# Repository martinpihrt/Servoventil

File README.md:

# Servoventil
Servoventil pro zalévací systém řízený procesorem ATTINY 1634 napájený z 5 AA baterií (celkem 6V). Zařízení je postavené z SMD součástek jako finální produkt za co nejméně peněz. Schéma zapojení obsahuje pouze nejnutněší součástky a procesor, který není zbytečně velký (rozměrově a programově). Deska obsahuje DIP spínač pro nastavení časů.  Programovací konektor ICSP 2x5 pinů, LED signalizující vybité baterie a chod zařízení, konektor pro připojení serva MG996R, startovací tlačítko, konektor pro sériovou linku (možnost komunikace s procesorem). Program pro procesor je napsán v prostředí Arduino IDE.  
Cena celého zařízení vychází bez serva na cca 225 Kč.

* Pohled na osazenou desku HW:1.0
<br>
* Schéma zapojení HW:1.0
<br>

# Funkce
## Uvedení do provozu
Po připojení napájení (5ks nabíjecí baterie AA 1,2V - celkem tedy 6-7V) čeká zařízení na stisk tlačítka. V tomto režimu neodebírá žádný proud z baterií (oba MOSFET tranzistory jsou udržovány uzavřené přes rezistory z kladného pólu). Časovač RTC ještě nebyl nastaven a má vloženu záložní baterii. Po stisknutí tlačítka na minimálně 1 sec se uzemní řídící vstup (gate) MOSFET tranzistoru, ten se otevře a přivede napájecí napětí na stabilizátor 3,3V. Za stabilizátorem je připojen procesor ATTINY 1634, který provede toto:
* sepne pomocný tranzistor, který podrží sepnutý (gate) u MOSFETu i po uvolnění tlačítka.
* změří napětí baterie (na AD vstupu procesoru je napětí z baterií 0-6V sníženo rezistorovým děličem na rozsah 0-3,3V). Napětí baterie se pohybuje (naprázdno) plně nabitého článku 1,4 V až napětí vybitého článku 1,0 V. Napětí pod 5V lze považovat za vybitý stav. Na AD vstupu naměříme hodnotu napětí (po zmenšení děličem) 2,6V. Pokud je baterie vybitá bliká LED dioda (3x blik, pauza, 3x blik...). RTC běží pouze z baterie a když je čas alarmu tak RTC přes svůj vnitřní tranzistor (otevřený kolektor) uzemní MOSFET, který sepne napájení pro stabilizátor a CPU. 
* přečte nastavené DIP spínače, sepne na určitý čas servo (napájení serva přes MOSFET a generuje signál pro odpovýdající směr a rychlost serva na určitou dobu) LED svítí -> ventil se otevře. Následně vypne napájení serva a čeká nastavenou dobu (dle DIP spínače 1-7 minut). Led bliká po dobu čekání otevření ventilu (krátké záblesky). Po nastavené době opět sepne napájení serva a ventil uzavře (LED svítí).
* nastaví čas (alarm) do RTC pro příští probuzení zařízení (cyklus 12, nebo 24 hodin).
* vypne veškeré napájení (běží pouze RTC z baterie).
* po nastavené době (DIP pozice 4: 12/24 hodin) RTC probudí CPU a opět se provede otevření ventilu na určitou dobu...

## DIP spínač má následující význam
Pozice 1-3 je BCD (dvojkový) kód pro nastvení doby otevření ventilu 1-7 minut.
* pozice 1 -> ON=1 minuta
* pozice 2 -> ON=2 minuty
* pozice 3 -> ON=4 minuty
Výsledný čas dle pozice 1-3 se sčítá. Příklad: čas otevření ventilu chceme 3 minuty -> DIP pozice 1 = ON, pozice 2 = ON, pozice 3 = OFF

Pozice 4 je čas probouzení.
* pozice 4 -> ON= 12 hodin, OFF= 24 hodin probouzení RTC časovače.

## Osazení desky spojů
Deska byla vyrobena u https://www.allpcb.com/.
* Pohled na desku TOP
<br>
* Pohled na desku BOT
<br>
První čím začneme je osazení SMD součástek z horní strany (TOP) a následně spodní (BOTTOM) strany. Po osazení SMD součástek zapájíme z horní strany THT (drátové) součástky - DIP spínače, držák baterie, napájecí konektor, řadové lišty. Před připojením napájení (baterie, nebo ICSP konektor) je potřeba desku pečlivě zkontrolovat na případné zkraty, nebo otočení součástek. Značení SMD rezistorů je následující: příklad text na rezistoru 1014 znamená 101 + 4 nuly tedy 101 0000 Ohmů, nebo 202 znamená 20 + 2 nuly tedy 20 00 Ohmů (2k).
Před připojením baterií (5ks AA) připojíme (pokud máme) napájecí zdroj s proudovou pojistkou, kterou nastavíme na 100 mA při 6V. Servo ani ICSP programátor není zatím k desce připojen. Obvod nemá v tuto chvíli ze zdroje odebírat žádný proud. Stiskneme a držíme tlačítko SW1 zmačknuté. Multimetrem (voltmetrem) změříme napětí na procesoru, RTC nebo stabilizátoru 3,3V. Napětí musí být cca 3,3V (při 6V na zdroji). Proud ze zdroje bude stále nepatrný (pár mA) - pouze se napájí procesor. Pokud se neobjevil problém (zkrat, velký podezřelý odběr proudu ze zdroje atd...) můžeme odpojit zdroj a zkusit připojit ICSP programátor. Nastavíme Arduino IDE na správný procesor a ICSP programátor. V tuto chvíli by již měl jít do procesoru nahrávat kód. Pokud připojíme na UART (sériovou linku) převodník, můžeme sledovat ladící výpisy co se aktuálně v procesoru odehrává. Protože je RTC obvod DS3231 jako samostatná součástka velmi drahý (okolo 200,-), tak ho odpájíme z China desky (ta se dá pořídit za 30,-).
* Pohled na osazenou desku TOP
<br>
* Pohled na osazenou desku BOT
<br>
* Připojení ICSP programátoru a USB-UART převodníku
<br>
<br>
* Deska RTC s DS3231 (před vypájením a po vypájení)
<br>
<br>

## Přidání podpory pro procesor ATTINY 1634 do Arduino IDE
Spustíme nainstalované Arduino v našem počítači a otevřeme záložku "Soubor -> vlastnosti" a do správce dalších desek URL přidáme tento odkaz
http://drazzy.com/package_drazzy.com_index.json ze stránek [GitHub drazzy](https://github.com/SpenceKonde/ATTinyCore/blob/master/Installation.md). Následně potvrdíme tlačítkem "OK". Otevřeme v Arduinu záložku "Nástroje -> Vývojová deska -> Manažér desek" v otevřeném seznamu si vybereme "ATTinyCore by Spencle Konde" a přidáme do Arduina tlačítkem "instalace". V nastavení Arduino IDE je po těchto krocích možné využívat i jiné procesory než které jsou ve výchozí instalaci Arduina.

## Nahrání programu do desky - ICSP programátor
Připojíme do konektoru ICSP desky servoventilu náš programátor (pokud ho nemáme zakoupený, můžeme si ho vyrobit dle [tohoto návodu](https://pihrt.com/elektronika/390-programator-atmel-isp-usbasp)). Při připojení programátoru nepoužíváme napájení z baterií (baterie odpojíme)!

# Verze FW
* 1.0.0 výchozí verze programu 
* 0.0.0 výchozí verze programu - test všech periferií

# Verze HW
* 1.0 15.1.2019 výchozí verze desky 

# Licence
Creative Commons Attribution Share Alike 4.0
cc-by-sa-4.0

Na projektu se podílejí:
HW a FW Martin Pihrt - www.pihrt.com

# Aktuálně, TODO
## 23.4.2020
* Pracuji na verzi FW 1.0.0 (funkce dle popisu DIP a uvedení do provozu)

## 18.2.2019
* HW je otestován a plně funkční: pro test použit FW:0.0.0. Článek NiMh má 1,2 V. Napětí (naprázdno) plně nabitého článku je 1,4 V. Napětí vybitého článku je 1,0 V. Máme 5 článků -> napětí se bude pohybovat od 5V do 7V. Pod 5V je vybito LED blikne 2x krátce. Běží program - LED bliká rychle.

Výpis ze seriové linky (2 minuty probouzení)  
FW:0.0.0,18.2.2019,11:13:33  
RTC init...OK  
DIP1-4 init...OK  
DIP1=0 DIP2=1 DIP3=0 DIP4=1  
Baterie=5.86V  
Servo init...OK  
RTC nastavuji interval...OK  
Baterie=5.78V  
Baterie=5.85V  
Vypinam!

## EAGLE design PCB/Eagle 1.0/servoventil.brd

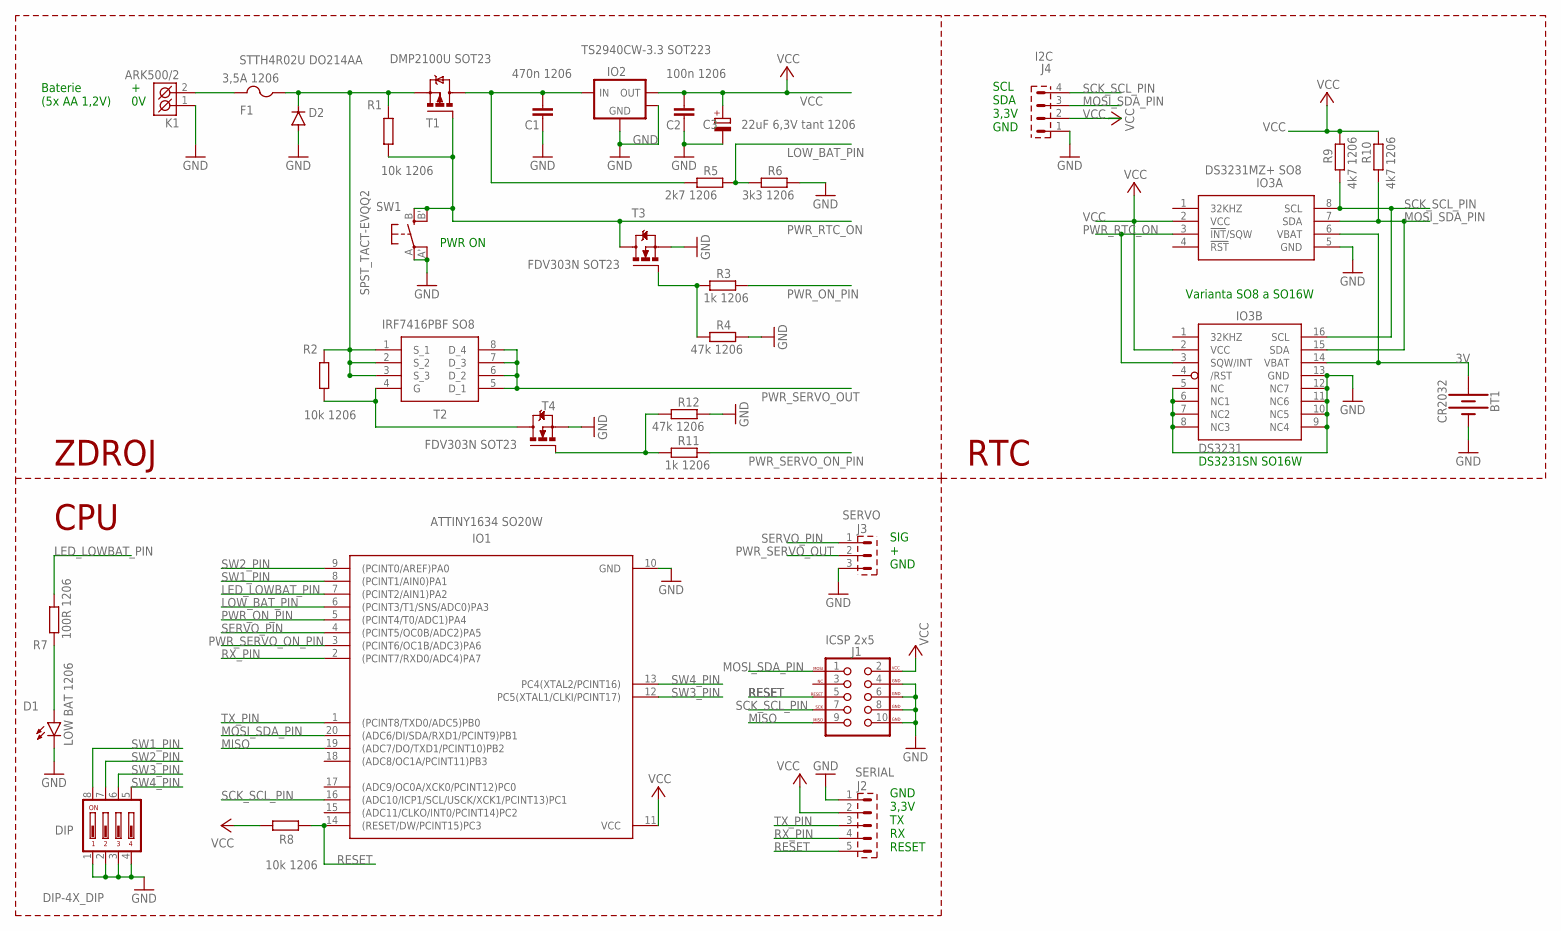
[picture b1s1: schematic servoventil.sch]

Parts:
BT1: CR2032; BATTCOM_20MM_PTH
C1: 470n 1206; C1206
C2: 100n 1206; C1206
C3: 22uF 6,3V tant 1206; CT3216
D1: LOW BAT 1206; LED-1206
D2: STTH4R02U DO214AA; DO214AA
DIP: DIP-4X_DIP; DIP-4X
F1: 3,5A 1206; R1206
IO1: ATTINY1634 SO20W; SOIC20
IO2: TS2940CW-3.3 SOT223; SOT-223-3
IO3A: DS3231MZ+ SO8; SOIC127P600X175-8N
IO3B: DS3231SN SO16W; SO16W
J1: ICSP 2x5; 2X5-SHROUDED_LOCK
J2: SERIAL; S1G5_JUM
J3: SERVO; S1G3_JUM
J4: I2C; S1G4_JUM
K1: ARK500/2
R1, R2, R8: 10k 1206; R1206
R3, R11: 1k 1206; R1206
R4, R12: 47k 1206; R1206
R5: 2k7 1206; R1206
R6: 3k3 1206; R1206
R7: 100R 1206; R1206
R9, R10: 4k7 1206; R1206
SW1: SPST_TACT-EVQQ2; EVQ-Q2
T1: DMP2100U SOT23; SOT-23
T2: IRF7416PBF SO8; SOIC127P600X175-8N
T3, T4: FDV303N SOT23; SOT-23

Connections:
3V: BT1.1 (+), IO3A.6 (VBAT), IO3B.14 (VBAT)
6V: C1.1, IO2.1 (VIN), R5.2, T1.3 (D)
GND: BT1.2 (-), C1.2, C2.2, C3.-, D1.C, D2.A, DIP.1, DIP.2, DIP.3, DIP.4, IO1.10 (GND), IO2.2 (GND), IO2.4 (HEATSINK), IO3A.5 (GND), IO3B.5 (NC), IO3B.6 (NC1), IO3B.7 (NC2), IO3B.8 (NC3), IO3B.9 (NC4), IO3B.10 (NC5), IO3B.11 (NC6), IO3B.12 (NC7), IO3B.13 (GND), J1.4 (GND), J1.6 (GND), J1.8 (GND), J1.10 (GND), J2.1, J3.3, J4.1, K1.1 (K1), R4.1, R6.1, R12.1, SW1.A, SW1.A' (P1), T3.2 (S), T4.2 (S)
LED_LOWBAT_PIN: IO1.7 ((PCINT2/AIN1)PA2), R7.1
LOW_BAT_PIN: IO1.6 ((PCINT3/T1/SNS/ADC0)PA3), R5.1, R6.2
MISO: IO1.19 ((ADC7/DO/TXD1/PCINT10)PB2), J1.9 (MISO)
MOSI_SDA_PIN: IO1.20 ((ADC6/DI/SDA/RXD1/PCINT9)PB1), IO3A.7 (SDA), IO3B.15 (SDA), J1.1 (MOSI), J4.3, R10.2
unnamed: F1.2, K1.2 (K2)
unnamed: D2.C, F1.1, R1.2, R2.2, T1.2 (S), T2.1 (S_1), T2.2 (S_2), T2.3 (S_3)
unnamed: R3.2, R4.2, T3.1 (G)
unnamed: R2.1, T2.4 (G), T4.3 (D)
unnamed: R11.2, R12.2, T4.1 (G)
unnamed: D1.A, R7.2
PWR_ON_PIN: IO1.5 ((PCINT4/T0/ADC1)PA4), R3.1
PWR_RTC_ON: IO3A.3 (!INT!/SQW), IO3B.3 (SQW/INT), R1.1, SW1.B (S), SW1.B' (S1), T1.1 (G), T3.3 (D)
PWR_SERVO_ON_PIN: IO1.3 ((PCINT6/OC1B/ADC3)PA6), R11.1
PWR_SERVO_OUT: J3.2, T2.5 (D_1), T2.6 (D_2), T2.7 (D_3), T2.8 (D_4)
RESET: IO1.14 ((RESET/DW/PCINT15)PC3), J1.5 (RESET), J2.5, R8.2
RX_PIN: IO1.2 ((PCINT7/RXD0/ADC4)PA7), J2.4
SCK_SCL_PIN: IO1.16 ((ADC10/ICP1/SCL/USCK/XCK1/PCINT13)PC1), IO3A.8 (SCL), IO3B.16 (SCL), J1.7 (SCK), J4.4, R9.2
SERVO_PIN: IO1.4 ((PCINT5/OC0B/ADC2)PA5), J3.1
SW1_PIN: DIP.8, IO1.8 ((PCINT1/AIN0)PA1)
SW2_PIN: DIP.7, IO1.9 ((PCINT0/AREF)PA0)
SW3_PIN: DIP.6, IO1.12 (PC5(XTAL1/CLKI/PCINT17))
SW4_PIN: DIP.5, IO1.13 (PC4(XTAL2/PCINT16))
TX_PIN: IO1.1 ((PCINT8/TXD0/ADC5)PB0), J2.3
VCC: C2.1, C3.+, IO1.11 (VCC), IO2.3 (VOUT), IO3A.2 (VCC), IO3B.2 (VCC), J1.2 (VCC), J2.2, J4.2, R8.1, R9.1, R10.1

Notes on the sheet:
+ 0V
Baterie (5x AA 1,2V)
ZDROJ
CPU
RTC
GND 3,3V TX RX RESET
PWR ON
Varianta SO8 a SO16W
DS3231SN SO16W
SIG + GND
SCL SDA 3,3V GND

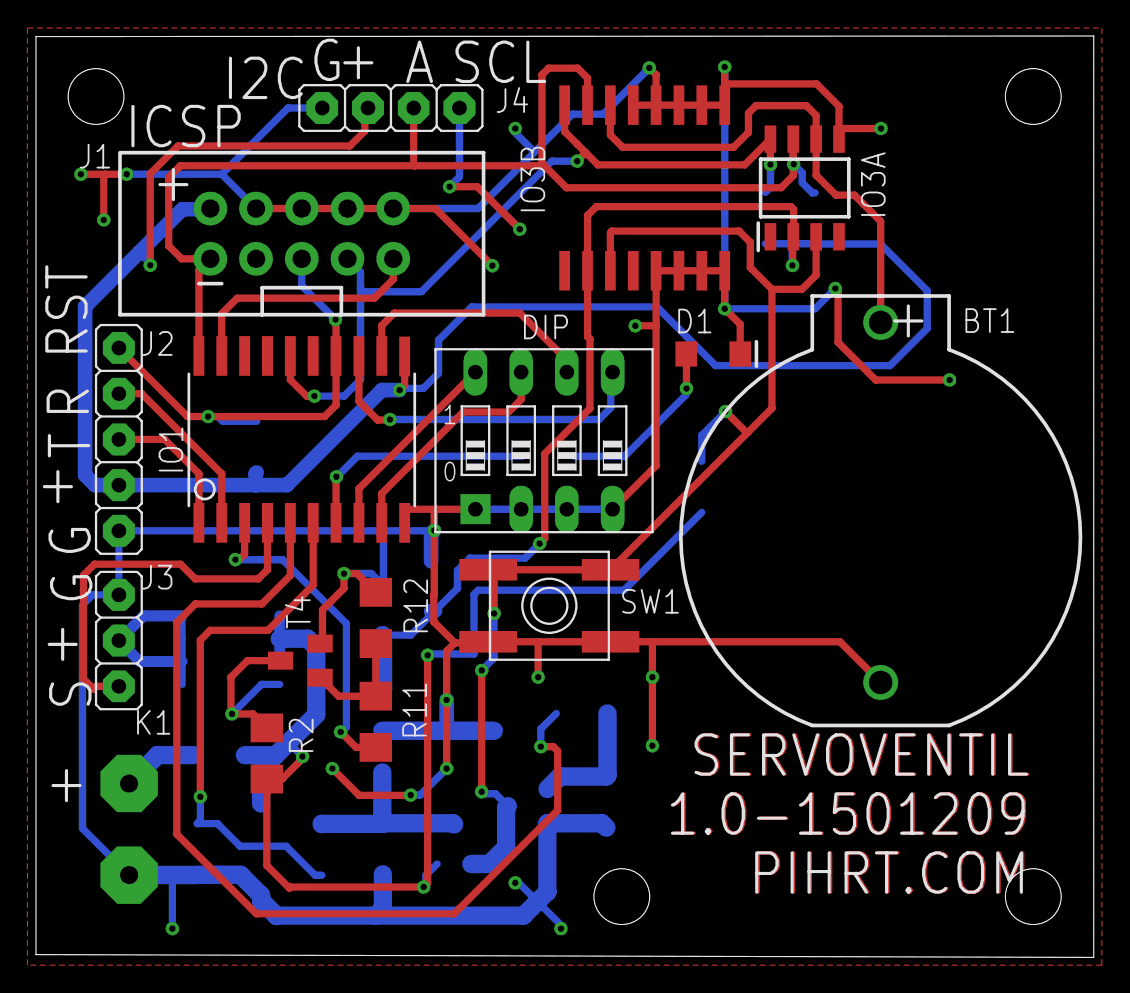
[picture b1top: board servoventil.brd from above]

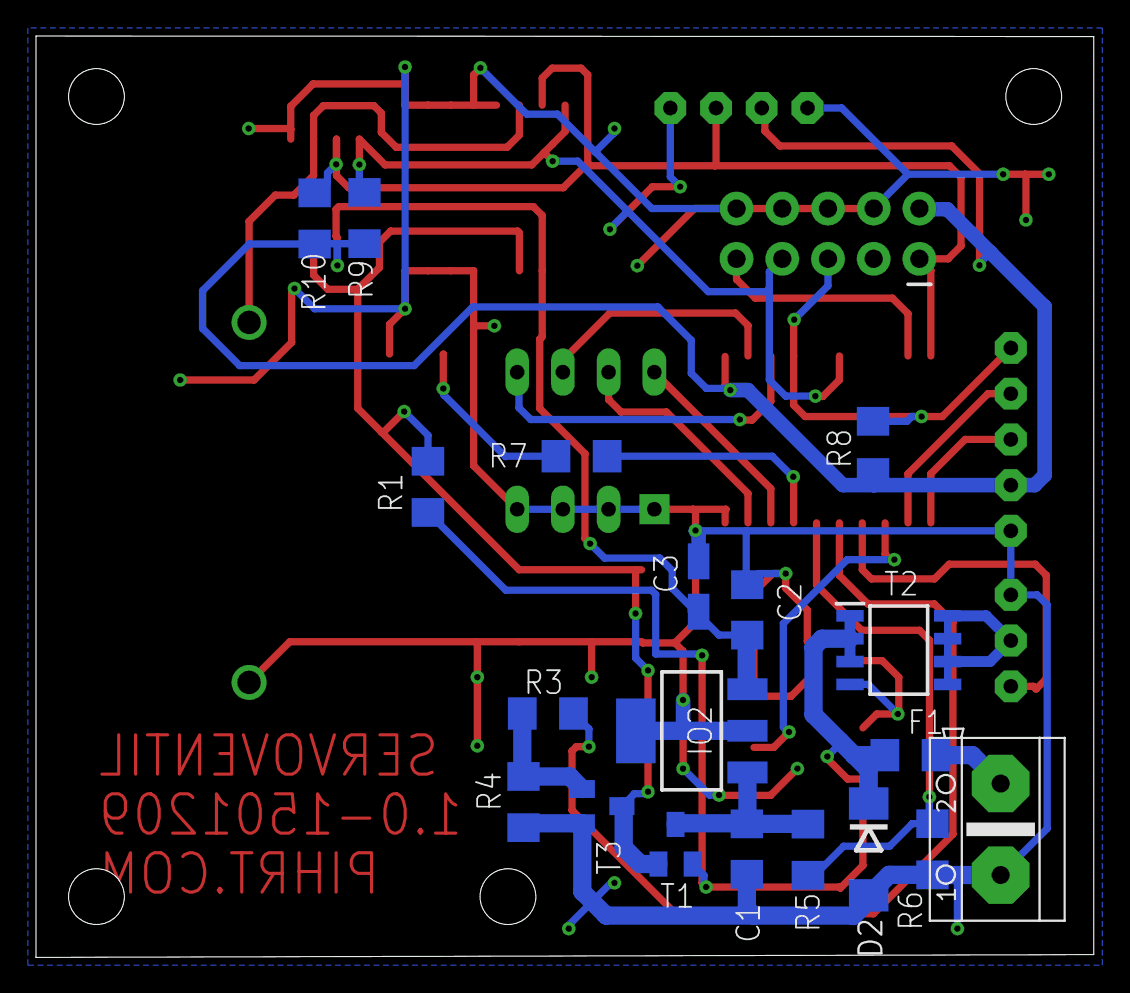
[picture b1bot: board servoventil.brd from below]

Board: 2 copper layers, 58.8 x 51.2 mm, 34 parts (19 on the bottom side), 27 nets.

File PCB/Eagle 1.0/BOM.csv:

"Part";"Value";"Device";"Package";"Description";"";
"BT1";"CR2032";"BATTERY-20MM_PTH";"BATTCOM_20MM_PTH";"Battery - Single Cell";"";
"C1";"470n 1206";"C-EUC1206";"C1206";"CAPACITOR, European symbol";"";
"C2";"100n 1206";"C-EUC1206";"C1206";"CAPACITOR, European symbol";"";
"C3";"22uF 6,3V tant 1206";"CPOL-EUCT3216";"CT3216";"POLARIZED CAPACITOR, European symbol";"";
"D1";"LOW BAT 1206";"LED1206";"LED-1206";"LED (Generic)";"";
"D2";"STTH4R02U  DO214AA";"DIODE-DO214AA";"DO214AA";"DIODE";"";
"DIP";"DIP-4X_DIP";"DIP-4X_DIP";"DIP-4X";"DIP Prepinac - 4x";"";
"F1";"3,5A 1206";"PTCFUSE-1206";"R1206";"PTC fuses, resettable thermistors";"";
"IO1";"ATTINY1634 SO20W";"ATTINY1634-SU";"SOIC20";"ATtiny1634";"";
"IO2";"TS2940CW-3.3 SOT223";"MCP1825_SOT223";"SOT-223-3";"Microchip MCP1824 LDO Voltage Regulator";"";
"IO3A";"DS3231MZ+ SO8";"DS3231MZ+";"SOIC127P600X175-8N";"Real Time Clock 5+/-ppm RTC";"";
"IO3B";"DS3231SN SO16W";"DS3231/SO";"SO16W";"";"";
"J1";"ICSP 2x5";"AVR_SPI_PROG_5X2LOCK";"2X5-SHROUDED_LOCK";"AVR 10-pin ICSP Header";"";
"J2";"SERIAL";"S1G5_JUMP";"S1G5_JUM";"Radove konektory - koliky - 5x";"";
"J3";"SERVO";"S1G3_JUMP";"S1G3_JUM";"Radove konektory - koliky - 3x";"";
"J4";"I2C";"S1G4_JUMP";"S1G4_JUM";"Radove konektory - koliky - 4x";"";
"K1";"ARK500/2";"ARK500/2";"ARK500/2";"Svorkovnice - roztec 5mm - dvojita";"";
"R1";"10k 1206";"R-EU_R1206";"R1206";"RESISTOR, European symbol";"";
"R2";"10k 1206";"R-EU_R1206";"R1206";"RESISTOR, European symbol";"";
"R3";"1k 1206";"R-EU_R1206";"R1206";"RESISTOR, European symbol";"";
"R4";"47k 1206";"R-EU_R1206";"R1206";"RESISTOR, European symbol";"";
"R5";"2k7 1206";"R-EU_R1206";"R1206";"RESISTOR, European symbol";"";
"R6";"3k3 1206";"R-EU_R1206";"R1206";"RESISTOR, European symbol";"";
"R7";"100R 1206";"R-EU_R1206";"R1206";"RESISTOR, European symbol";"";
"R8";"10k 1206";"R-EU_R1206";"R1206";"RESISTOR, European symbol";"";
"R9";"4k7 1206";"R-EU_R1206";"R1206";"RESISTOR, European symbol";"";
"R10";"4k7 1206";"R-EU_R1206";"R1206";"RESISTOR, European symbol";"";
"R11";"1k 1206";"R-EU_R1206";"R1206";"RESISTOR, European symbol";"";
"R12";"47k 1206";"R-EU_R1206";"R1206";"RESISTOR, European symbol";"";
"SW1";"SPST_TACT-EVQQ2";"SPST_TACT-EVQQ2";"EVQ-Q2";"SMT 6mm switch, EVQQ2 series";"";
"T1";"DMP2100U SOT23";"MOSFET-P-SOT23";"SOT-23";"P-Channel MOSFET with integrated body diode";"";
"T2";"IRF7416PBF SO8";"IRF7416PBF";"SOIC127P600X175-8N";"MOSFET P-Channel 30V 10A HEXFET SOIC8 Infineon IRF7416PBF P-channel MOSFET Transistor, 10 A, 30 V, 8-Pin SOIC";"";
"T3";"FDV303N SOT23";"MOSFET-N-SOT23";"SOT-23";"N-Channel MOSFET";"";
"T4";"FDV303N SOT23";"MOSFET-N-SOT23";"SOT-23";"N-Channel MOSFET";"";

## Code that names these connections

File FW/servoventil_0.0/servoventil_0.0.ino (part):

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#define FW    "0.0.0"  // aktuální verze FW 18.2.2019

// přiřazení pinů na procesoru ATTINY 1634
//#define SCK_SCL_PIN      12 // PC1 pin 16 pro info  (SCK je na stejném vodiči jako SCL)
//#define MOSI_SDA_PIN     16 // PB1 pin 20 pro info  (MOSI je na stejném vodiči jako SDA)
//#define RX_PIN           1  // PA7 pin 2  pro info
//#define TX_PIN           0  // PB0 pin 1  pro info
#define PWR_SERVO_ON_PIN   2  // PA6 pin 3  spíná napájení serva
#define SERVO_PIN          3  // PA5 pin 4  výstup pro servo PWM
#define PWR_ON_PIN         4  // PA4 pin 5  spíná samodržení napájení procesoru
#define LOW_BAT_PIN        A0 // PA3 pin 6  jako A0 vstup z baterie, že je málé napájení baterie
#define LED_LOWBAT_PIN     6  // PA2 pin 7  výstup pro LED, že je málé napájení baterie
#define SW1_PIN            7  // PA1 pin 8  vstup DIP přepínač 1
#define SW2_PIN            8  // PA0 pin 9  vstup DIP přepínač 2
#define SW3_PIN            9  // PC5 pin 12 vstup DIP přepínač 3
#define SW4_PIN            10 // PC4 pin 13 vstup DIP přepínač 4

#include <avr/wdt.h>  // watchdog

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
void getBATT(){
 #ifdef USE_AD 
   int in = analogRead(LOW_BAT_PIN);
   volt = (in * 6.0) / 1024.0; // při 6V je za děličem 3.3V tedy 1023 max Ubat
   #ifdef DEBUG
     DPRINT("Baterie");
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//******************************************************************************************************************************

void setup() { // nastavení
  pinMode(PWR_ON_PIN,OUTPUT);         // pin pro samodržení napájení CPU
  pinMode(PWR_SERVO_ON_PIN,OUTPUT);   // pin pro napájení serva
  pinMode(SERVO_PIN,OUTPUT);          // pin pro PWM serva
  pinMode(LED_LOWBAT_PIN,OUTPUT);     // pin pro LED
  pinMode(LOW_BAT_PIN,INPUT);         // pin na AD
  pinMode(SW1_PIN,INPUT_PULLUP);      // pin DIP1 
  pinMode(SW2_PIN,INPUT_PULLUP);      // pin DIP2
  pinMode(SW3_PIN,INPUT_PULLUP);      // pin DIP3
  pinMode(SW4_PIN,INPUT_PULLUP);      // pin DIP4
  
  digitalWrite(PWR_ON_PIN,HIGH);      // podržet napájení (po uvolnění tlačítka
  
  digitalWrite(PWR_SERVO_ON_PIN,LOW); // vypnout napájení serva
  digitalWrite(SERVO_PIN,LOW);        // vypnout výstup pro PWM serva      
  digitalWrite(LED_LOWBAT_PIN,HIGH);  // zapnout LED

  wdt_enable(WDTO_2S);                // povolit watchdog ping 2s
  wdt_reset();                        // vynulovat časovač pro wdt
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     DPRINT("DIP1-4 init...");
     DPRINTLN("OK");
     DPRINT("DIP1=");
     DPRINT(digitalRead(SW1_PIN));DPRINT(" DIP2=");DPRINT(digitalRead(SW2_PIN));DPRINT(" DIP3=");DPRINT(digitalRead(SW3_PIN));DPRINT(" DIP4=");DPRINTLN(digitalRead(SW4_PIN));
  #endif
  
  #ifdef USE_AD
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    }// konec if
    
    while(volt<5.0){ // je malé napětí baterie budeme neustále točit a dál nic nebude dokud bat >5V
       digitalWrite(LED_LOWBAT_PIN,HIGH);   // zapnout LED
       delay(50);
       digitalWrite(LED_LOWBAT_PIN,LOW);    // vypnout LED
       delay(50);
       digitalWrite(LED_LOWBAT_PIN,HIGH);   // zapnout LED
       delay(50);
       digitalWrite(LED_LOWBAT_PIN,LOW);    // vypnout LED
       delay(1000);
       getBATT();
       wdt_reset();                        // vynulovat časovač pro wdt
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     #ifdef DEBUG
        DPRINT("Servo init...");
     #endif
     pinMode(PWR_SERVO_ON_PIN,OUTPUT);      // napájení serva výstupní pin
     digitalWrite(PWR_SERVO_ON_PIN, HIGH);  // zapnout napájení serva
     delay(100);
     servo.attach(SERVO_PIN);               // aktivovat servo
     #ifdef DEBUG
        DPRINTLN("OK");
     #endif
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    #endif
  #endif
      
  digitalWrite(LED_LOWBAT_PIN,LOW);         // vypnout LED
  wdt_reset();                        // vynulovat časovač pro wdt
}//konec setup

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    previousMillis = currentMillis;
// test serva, blikání LED, měření baterie
    if(test==1 or test==90 or test==180) getBATT();  
    digitalWrite(LED_LOWBAT_PIN,!digitalRead(LED_LOWBAT_PIN)); // blikame LED
    if(test<180) test++;
    if(test==180) {
      set_next_alarm();                      // nastavit kdy se probudi CPU podle DIP
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        delay(1000);
        wdt_reset();                        // vynulovat časovač pro wdt
      #endif
      digitalWrite(SERVO_PIN,LOW);           // vypnout výstup pro PWM serva
      digitalWrite(PWR_SERVO_ON_PIN,LOW);    // vypnout napájení serva
      digitalWrite(PWR_ON_PIN,LOW);          // vypnout napájení CPU
      while(1); // čekáme na reset od wdt
    }
  }//konec if
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
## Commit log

2019-01-10 Založení projektu
2019-01-11 Změna CPU
2019-01-12 Rozdělané schéma
2019-01-14 Schema před kontrolou
2019-01-14 Deska spojů, schéma
    vše před kontrolou (až dorazí součástky)
2019-01-15 Schéma a deska před kontrolou
2019-02-04 pcb foto
2019-02-05 add knihovny
2019-02-07 osazená deska
2019-02-07 otestovat
2019-02-09 další test
2019-02-16 oprava chyby na desce
    chyběla zem pod 3,3V stabilizátorem (heatsink + gnd se nespojilo)
2019-02-18 výchozí verze FW 0.0.0
    vše pracuje jak má :-)
2019-02-18 přidán výpis
    sériová linka
2019-02-18 final 0.0.0
2019-02-18 Já jsem hotov :-)
2019-02-19 final foto
2019-02-19 Přidáno schéma
2020-04-24 Netestované 24.4.2020 (beta)
2020-04-24 MG996R pro 3D

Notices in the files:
parts and their libraries:
SparkFun-LED: Licensing: Creative Commons ShareAlike 4.0 International - https://creativecommons.org/licenses/by-sa/4.0
Copyright (C) PaJa 2011-2014
